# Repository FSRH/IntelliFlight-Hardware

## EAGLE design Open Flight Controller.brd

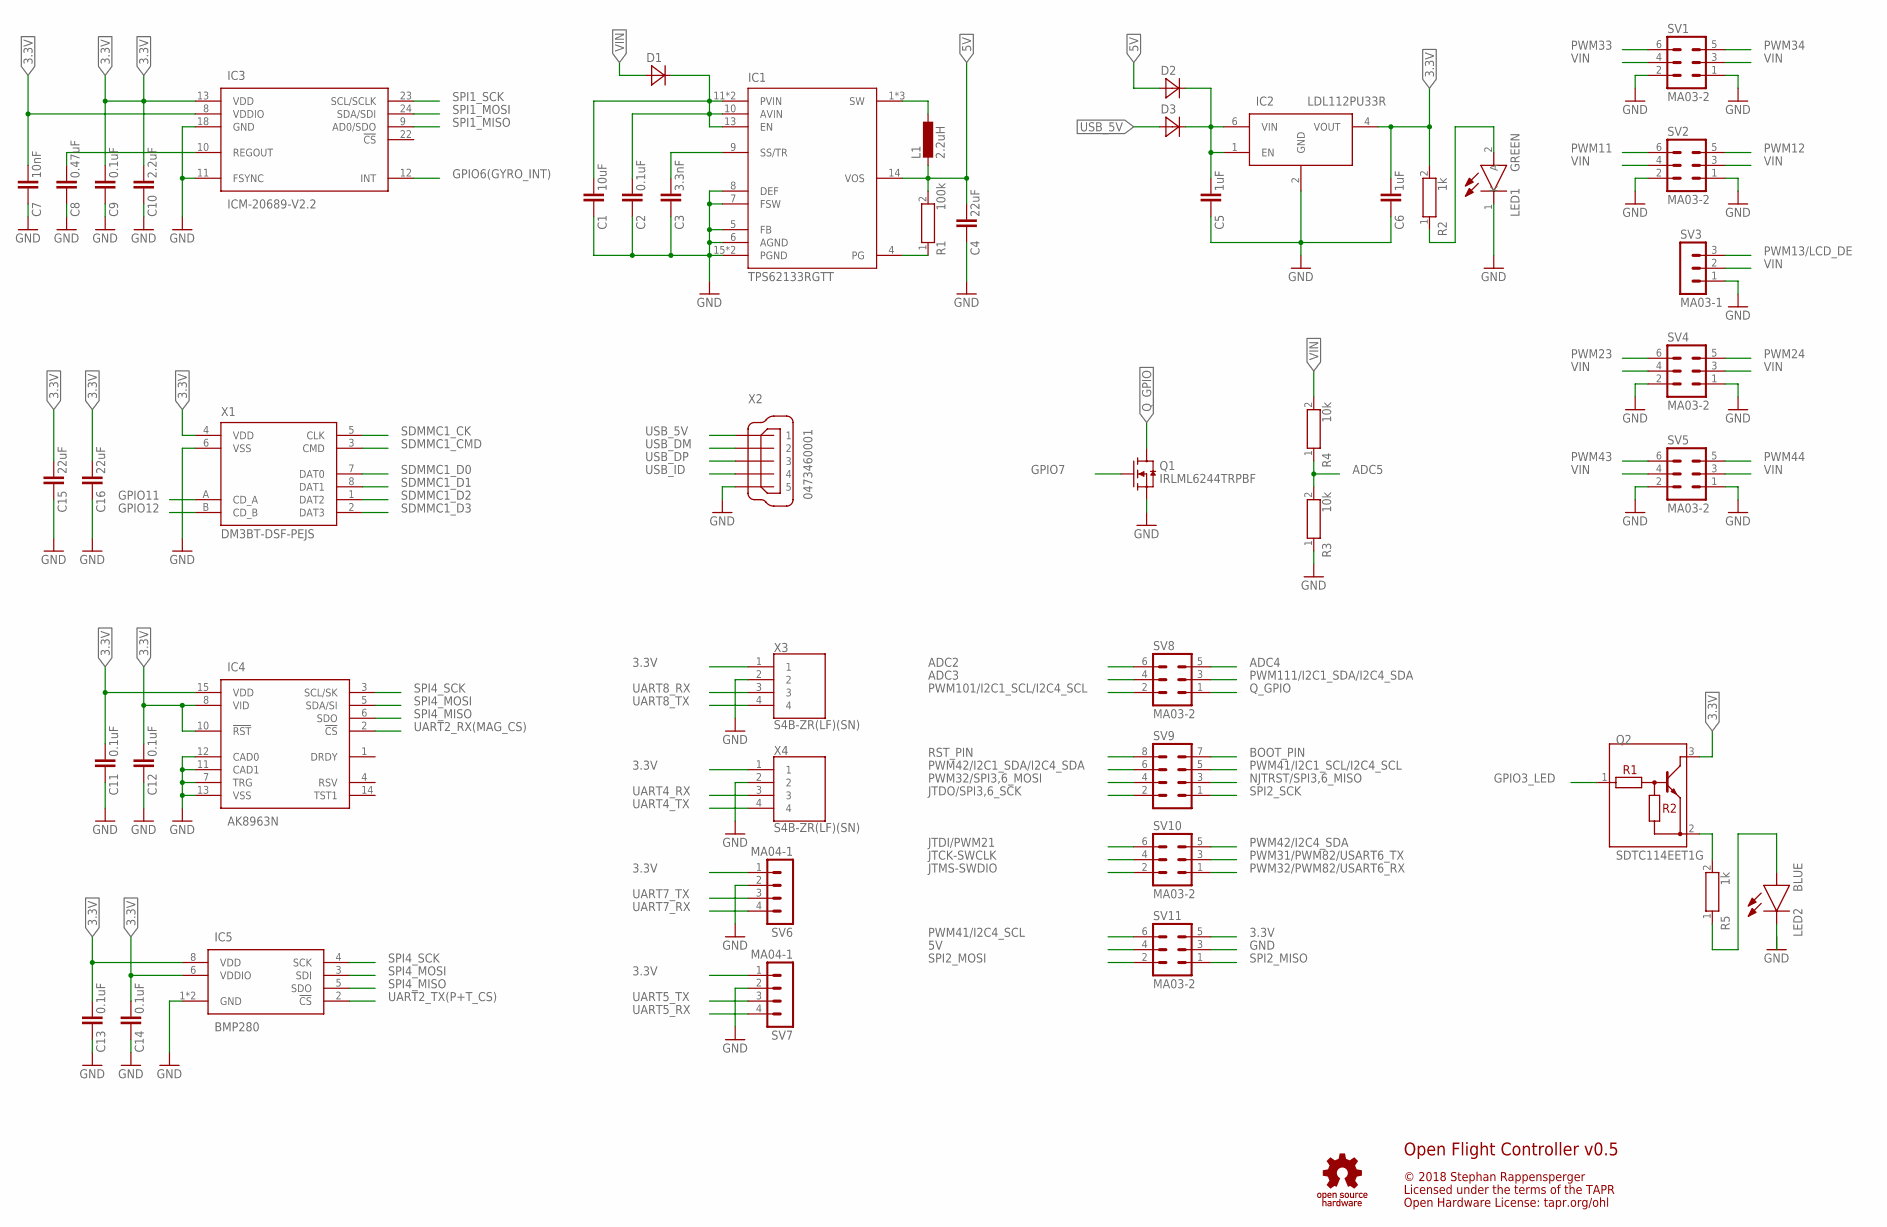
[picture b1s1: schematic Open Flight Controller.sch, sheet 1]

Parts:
C1: 10uF; CAPC1608X90N
C2, C9, C11, C12, C13, C14: 0.1uF; CAPC1608X90N
C3: 3.3nF; CAPC1608X90N
C4, C15, C16: 22uF; CAPC1608X100N
C5, C6: 1uF; CAPC1608X90N
C7: 10nF; CAPC1608X90N
C8: 0.47uF; CAPC1608X90N
C10: 2.2uF; CAPC1608X90N
D1, D2, D3: RBR3MM40ATR; PMDU
IC1: TPS62133RGTT; RGT16_1P7X1P7
IC2: LDL112PU33R; SON50P200X200X80-7N
IC3: ICM-20689-V2.2; QFN50P400X400X95-25N
IC4: AK8963N; QFN50P300X300X80-17N
IC5: BMP280; 8-PIN-METAL-LID-LGA
L1: 2.2uH; INDC2520X120N
LED1: GREEN; LEDC1608X100N
LED2: BLUE; LEDC1608X100N
Q1: IRLML6244TRPBF; SOT95P237X112-3N
Q2: SDTC114EET1G; SOT50P160X90-3N
R1: 100k; RESC1608X50N
R2, R5: 1k; RESC1608X50N
R3, R4: 10k; RESC1608X50N
SV1, SV2, SV4, SV5, SV8, SV10, SV11: MA03-2
SV3: MA03-1
SV6, SV7: MA04-1
SV9: MA04-2
X1: DM3BT-DSF-PEJS
X2: 0473460001
X3, X4: S4B-ZR(LF)(SN); SHDR4W50P0X150_1X4_750X600X370

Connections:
3.3V: C6.1, C7.1, C9.1, C10.1, C11.1, C12.1, C13.1, C14.1, C15.1, C16.1, IC2.4 (VOUT), IC3.8 (VDDIO), IC3.13 (VDD), IC4.8 (VID), IC4.10 (!RST), IC4.15 (VDD), IC5.6 (VDDIO), IC5.8 (VDD), Q2.3 (C), R2.2, SV6.1, SV7.1, SV11.5, X1.4 (VDD), X3.1, X4.1; also elsewhere on the board
5V: C4.1, D2.1 (A), IC1.14 (VOS), L1.1, R1.2, SV11.4
ADC2: SV8.6; also elsewhere on the board
ADC3: SV8.4; also elsewhere on the board
ADC4: SV8.5; also elsewhere on the board
ADC5: R3.2, R4.1; also elsewhere on the board
BOOT_PIN: SV9.7; also elsewhere on the board
GND: C1.2, C2.2, C3.2, C4.2, C5.2, C6.2, C7.2, C8.2, C9.2, C10.2, C11.2, C12.2, C13.2, C14.2, C15.2, C16.2, IC1.5 (FB), IC1.6 (AGND), IC1.7 (FSW), IC1.8 (DEF), IC1.15 (PGND), IC1.16 (PGND), IC2.2 (GND), IC3.11 (FSYNC), IC3.18 (GND), IC4.7 (TRG), IC4.11 (CAD1), IC4.12 (CAD0), IC4.13 (VSS), IC5.1 (GND), IC5.7 (GND), LED1.1 (K), LED2.1 (K), Q1.2 (S), R3.1, SV1.1, SV1.2, SV2.1, SV2.2, SV3.1, SV4.1, SV4.2, SV5.1, SV5.2, SV6.2, SV7.2, SV11.3, X1.6 (VSS), X2.5, X3.2, X4.2; also elsewhere on the board
GPIO3_LED: Q2.1 (B); also elsewhere on the board
GPIO6(GYRO_INT): IC3.12 (INT); also elsewhere on the board
GPIO7: Q1.1 (G); also elsewhere on the board
GPIO11: X1.A (CD_A); also elsewhere on the board
GPIO12: X1.B (CD_B); also elsewhere on the board
JTCK-SWCLK: SV10.4; also elsewhere on the board
JTDI/PWM21: SV10.6; also elsewhere on the board
JTDO/SPI3,6_SCK: SV9.2; also elsewhere on the board
JTMS-SWDIO: SV10.2; also elsewhere on the board
unnamed: C1.1, C2.1, D1.2 (C), IC1.10 (AVIN), IC1.11 (PVIN), IC1.12 (PVIN), IC1.13 (EN)
unnamed: IC1.1 (SW), IC1.2 (SW), IC1.3 (SW), L1.2
unnamed: C3.1, IC1.9 (SS/TR)
unnamed: IC1.4 (PG), R1.1
unnamed: C5.1, D2.2 (C), D3.2 (C), IC2.1 (EN), IC2.6 (VIN)
unnamed: LED1.2 (A), R2.1
unnamed: C8.1, IC3.10 (REGOUT)
unnamed: Q2.2 (E), R5.2
unnamed: LED2.2 (A), R5.1
NJTRST/SPI3,6_MISO: SV9.3; also elsewhere on the board
PWM11: SV2.6; also elsewhere on the board
PWM12: SV2.5; also elsewhere on the board
PWM13/LCD_DE: SV3.3; also elsewhere on the board
PWM23: SV4.6; also elsewhere on the board
PWM24: SV4.5; also elsewhere on the board
PWM31/PWM82/USART6_TX: SV10.3; also elsewhere on the board
PWM32/PWM82/USART6_RX: SV10.1; also elsewhere on the board
PWM32/SPI3,6_MOSI: SV9.4; also elsewhere on the board
PWM33: SV1.6; also elsewhere on the board
PWM34: SV1.5; also elsewhere on the board
PWM41/I2C1_SCL/I2C4_SCL: SV9.5; also elsewhere on the board
PWM41/I2C4_SCL: SV11.6; also elsewhere on the board
PWM42/I2C1_SDA/I2C4_SDA: SV9.6; also elsewhere on the board
PWM42/I2C4_SDA: SV10.5; also elsewhere on the board
PWM43: SV5.6; also elsewhere on the board
PWM44: SV5.5; also elsewhere on the board
PWM101/I2C1_SCL/I2C4_SCL: SV8.2; also elsewhere on the board
PWM111/I2C1_SDA/I2C4_SDA: SV8.3; also elsewhere on the board
Q_GPIO: Q1.3 (D), SV8.1
RST_PIN: SV9.8; also elsewhere on the board
SDMMC1_CK: X1.5 (CLK); also elsewhere on the board
SDMMC1_CMD: X1.3 (CMD); also elsewhere on the board
SDMMC1_D0: X1.7 (DAT0); also elsewhere on the board
SDMMC1_D1: X1.8 (DAT1); also elsewhere on the board
SDMMC1_D2: X1.1 (DAT2); also elsewhere on the board
SDMMC1_D3: X1.2 (DAT3); also elsewhere on the board
SPI1_MISO: IC3.9 (AD0/SDO); also elsewhere on the board
SPI1_MOSI: IC3.24 (SDA/SDI); also elsewhere on the board
SPI1_SCK: IC3.23 (SCL/SCLK); also elsewhere on the board
SPI2_MISO: SV11.1; also elsewhere on the board
SPI2_MOSI: SV11.2; also elsewhere on the board
SPI2_SCK: SV9.1; also elsewhere on the board
SPI4_MISO: IC4.6 (SDO), IC5.5 (SDO); also elsewhere on the board
SPI4_MOSI: IC4.5 (SDA/SI), IC5.3 (SDI); also elsewhere on the board
SPI4_SCK: IC4.3 (SCL/SK), IC5.4 (SCK); also elsewhere on the board
UART2_RX(MAG_CS): IC4.2 (!CS); also elsewhere on the board
UART2_TX(P+T_CS): IC5.2 (!CS); also elsewhere on the board
UART4_RX: X4.3; also elsewhere on the board
UART4_TX: X4.4; also elsewhere on the board
UART5_RX: SV7.4; also elsewhere on the board
UART5_TX: SV7.3; also elsewhere on the board
UART7_RX: SV6.4; also elsewhere on the board
UART7_TX: SV6.3; also elsewhere on the board
UART8_RX: X3.3; also elsewhere on the board
UART8_TX: X3.4; also elsewhere on the board
USB_5V: D3.1 (A), X2.1
USB_DM: X2.2; also elsewhere on the board
USB_DP: X2.3; also elsewhere on the board
USB_ID: X2.4; also elsewhere on the board
VIN: D1.1 (A), R4.2, SV1.3, SV1.4, SV2.3, SV2.4, SV3.2, SV4.3, SV4.4, SV5.3, SV5.4

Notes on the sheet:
Open Flight Controller v0.5
© 2018 Stephan Rappensperger
Licensed under the terms of the TAPR
Open Hardware License: tapr.org/ohl

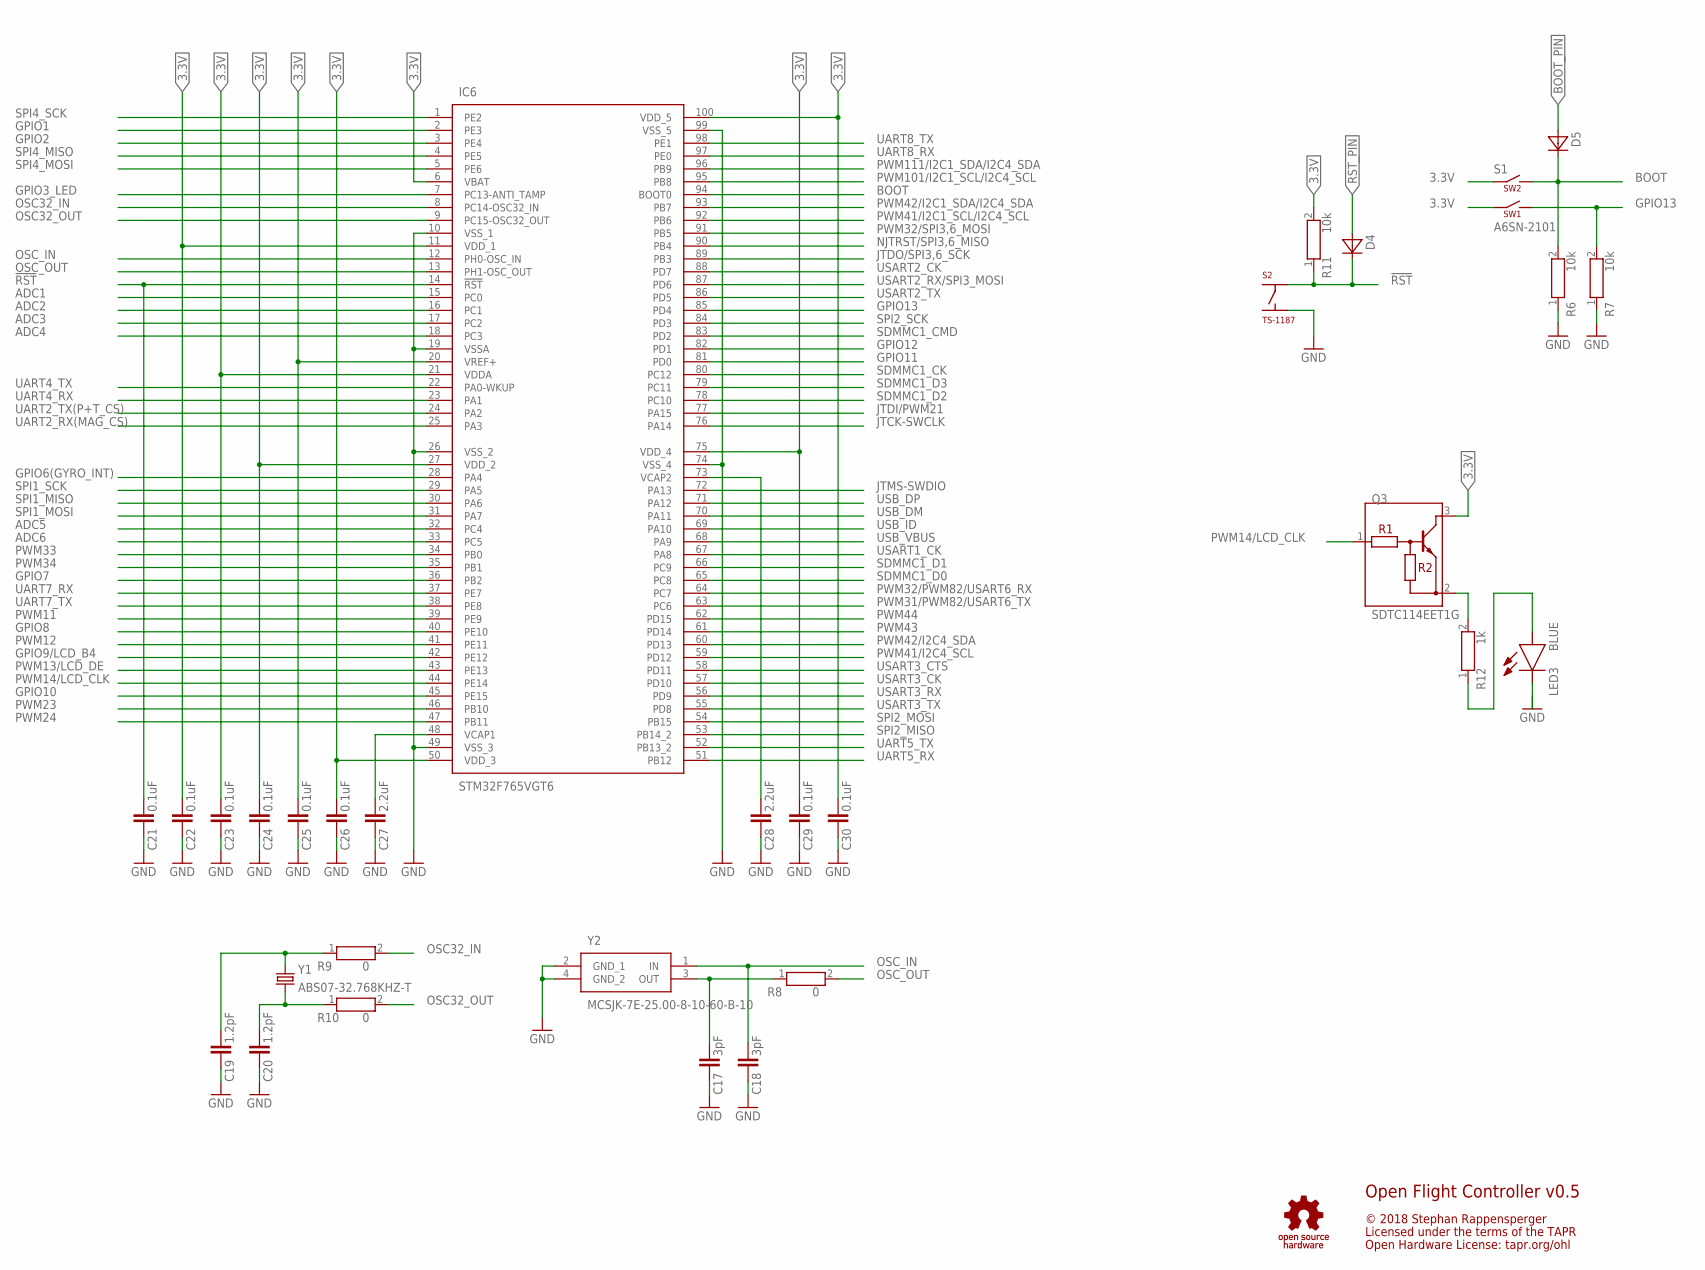
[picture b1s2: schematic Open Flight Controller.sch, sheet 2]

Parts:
C17, C18: 3pF; CAPC1608X90N
C19, C20: 1.2pF; CAPC1608X90N
C21, C22, C23, C24, C25, C26, C29, C30: 0.1uF; CAPC1608X90N
C27, C28: 2.2uF; CAPC1608X90N
D4, D5: RBR3MM40ATR; PMDU
IC6: STM32F765VGT6; QFP50P1600X1600X160-100N
LED3: BLUE; LEDC1608X100N
Q3: SDTC114EET1G; SOT50P160X90-3N
R6, R7, R11: 10k; RESC1608X50N
R8, R9, R10: 0; RESC1608X50N
R12: 1k; RESC1608X50N
S1: A6SN-2101; SOP254P930X455-4N
S2: TS-1187; TS-1187-3.8
Y1: ABS07-32.768KHZ-T; ABS-07
Y2: MCSJK-7E-25.00-8-10-60-B-10; MCSJK7E2500101060B10

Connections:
3.3V: C22.1, C23.1, C24.1, C25.1, C26.1, C29.1, C30.1, IC6.6 (VBAT), IC6.11 (VDD_1), IC6.20 (VREF+), IC6.21 (VDDA), IC6.27 (VDD_2), IC6.50 (VDD_3), IC6.75 (VDD_4), IC6.100 (VDD_5), Q3.3 (C), R11.2, S1.1 (COM_1), S1.2 (COM_2); also elsewhere on the board
!RST: C21.1, D4.2 (C), IC6.14 (!RST), R11.1, S2.P$2
ADC1: IC6.15 (PC0)
ADC2: IC6.16 (PC1); also elsewhere on the board
ADC3: IC6.17 (PC2); also elsewhere on the board
ADC4: IC6.18 (PC3); also elsewhere on the board
ADC5: IC6.32 (PC4); also elsewhere on the board
ADC6: IC6.33 (PC5)
BOOT: D5.2 (C), IC6.94 (BOOT0), R6.2, S1.4 (NO_1)
BOOT_PIN: D5.1 (A); also elsewhere on the board
GND: C17.2, C18.2, C19.2, C20.2, C21.2, C22.2, C23.2, C24.2, C25.2, C26.2, C27.2, C28.2, C29.2, C30.2, IC6.10 (VSS_1), IC6.19 (VSSA), IC6.26 (VSS_2), IC6.49 (VSS_3), IC6.74 (VSS_4), IC6.99 (VSS_5), LED3.1 (K), R6.1, R7.1, S2.P$4, Y2.2 (GND_1), Y2.4 (GND_2); also elsewhere on the board
GPIO1: IC6.2 (PE3)
GPIO2: IC6.3 (PE4)
GPIO3_LED: IC6.7 (PC13-ANTI_TAMP); also elsewhere on the board
GPIO6(GYRO_INT): IC6.28 (PA4); also elsewhere on the board
GPIO7: IC6.36 (PB2); also elsewhere on the board
GPIO8: IC6.40 (PE10)
GPIO9/LCD_B4: IC6.42 (PE12)
GPIO10: IC6.45 (PE15)
GPIO11: IC6.81 (PD0); also elsewhere on the board
GPIO12: IC6.82 (PD1); also elsewhere on the board
GPIO13: IC6.85 (PD4), R7.2, S1.3 (NO_2)
JTCK-SWCLK: IC6.76 (PA14); also elsewhere on the board
JTDI/PWM21: IC6.77 (PA15); also elsewhere on the board
JTDO/SPI3,6_SCK: IC6.89 (PB3); also elsewhere on the board
JTMS-SWDIO: IC6.72 (PA13); also elsewhere on the board
unnamed: C17.1, R8.1, Y2.3 (OUT)
unnamed: C27.1, IC6.48 (VCAP1)
unnamed: C28.1, IC6.73 (VCAP2)
unnamed: Q3.2 (E), R12.2
unnamed: C20.1, R10.1, Y1.2
unnamed: C19.1, R9.1, Y1.1
unnamed: LED3.2 (A), R12.1
NJTRST/SPI3,6_MISO: IC6.90 (PB4); also elsewhere on the board
OSC32_IN: IC6.8 (PC14-OSC32_IN), R9.2
OSC32_OUT: IC6.9 (PC15-OSC32_OUT), R10.2
OSC_IN: C18.1, IC6.12 (PH0-OSC_IN), Y2.1 (IN)
OSC_OUT: IC6.13 (PH1-OSC_OUT), R8.2
PWM11: IC6.39 (PE9); also elsewhere on the board
PWM12: IC6.41 (PE11); also elsewhere on the board
PWM13/LCD_DE: IC6.43 (PE13); also elsewhere on the board
PWM14/LCD_CLK: IC6.44 (PE14), Q3.1 (B)
PWM23: IC6.46 (PB10); also elsewhere on the board
PWM24: IC6.47 (PB11); also elsewhere on the board
PWM31/PWM82/USART6_TX: IC6.63 (PC6); also elsewhere on the board
PWM32/PWM82/USART6_RX: IC6.64 (PC7); also elsewhere on the board
PWM32/SPI3,6_MOSI: IC6.91 (PB5); also elsewhere on the board
PWM33: IC6.34 (PB0); also elsewhere on the board
PWM34: IC6.35 (PB1); also elsewhere on the board
PWM41/I2C1_SCL/I2C4_SCL: IC6.92 (PB6); also elsewhere on the board
PWM41/I2C4_SCL: IC6.59 (PD12); also elsewhere on the board
PWM42/I2C1_SDA/I2C4_SDA: IC6.93 (PB7); also elsewhere on the board
PWM42/I2C4_SDA: IC6.60 (PD13); also elsewhere on the board
PWM43: IC6.61 (PD14); also elsewhere on the board
PWM44: IC6.62 (PD15); also elsewhere on the board
PWM101/I2C1_SCL/I2C4_SCL: IC6.95 (PB8); also elsewhere on the board
PWM111/I2C1_SDA/I2C4_SDA: IC6.96 (PB9); also elsewhere on the board
RST_PIN: D4.1 (A); also elsewhere on the board
SDMMC1_CK: IC6.80 (PC12); also elsewhere on the board
SDMMC1_CMD: IC6.83 (PD2); also elsewhere on the board
SDMMC1_D0: IC6.65 (PC8); also elsewhere on the board
SDMMC1_D1: IC6.66 (PC9); also elsewhere on the board
SDMMC1_D2: IC6.78 (PC10); also elsewhere on the board
SDMMC1_D3: IC6.79 (PC11); also elsewhere on the board
SPI1_MISO: IC6.30 (PA6); also elsewhere on the board
SPI1_MOSI: IC6.31 (PA7); also elsewhere on the board
SPI1_SCK: IC6.29 (PA5); also elsewhere on the board
SPI2_MISO: IC6.53 (PB14_2); also elsewhere on the board
SPI2_MOSI: IC6.54 (PB15); also elsewhere on the board
SPI2_SCK: IC6.84 (PD3); also elsewhere on the board
SPI4_MISO: IC6.4 (PE5); also elsewhere on the board
SPI4_MOSI: IC6.5 (PE6); also elsewhere on the board
SPI4_SCK: IC6.1 (PE2); also elsewhere on the board
UART2_RX(MAG_CS): IC6.25 (PA3); also elsewhere on the board
UART2_TX(P+T_CS): IC6.24 (PA2); also elsewhere on the board
UART4_RX: IC6.23 (PA1); also elsewhere on the board
UART4_TX: IC6.22 (PA0-WKUP); also elsewhere on the board
UART5_RX: IC6.51 (PB12); also elsewhere on the board
UART5_TX: IC6.52 (PB13_2); also elsewhere on the board
UART7_RX: IC6.37 (PE7); also elsewhere on the board
UART7_TX: IC6.38 (PE8); also elsewhere on the board
UART8_RX: IC6.97 (PE0); also elsewhere on the board
UART8_TX: IC6.98 (PE1); also elsewhere on the board
USART1_CK: IC6.67 (PA8)
USART2_CK: IC6.88 (PD7)
USART2_RX/SPI3_MOSI: IC6.87 (PD6)
USART2_TX: IC6.86 (PD5)
USART3_CK: IC6.57 (PD10)
USART3_CTS: IC6.58 (PD11)
USART3_RX: IC6.56 (PD9)
USART3_TX: IC6.55 (PD8)
USB_DM: IC6.70 (PA11); also elsewhere on the board
USB_DP: IC6.71 (PA12); also elsewhere on the board
USB_ID: IC6.69 (PA10); also elsewhere on the board
USB_VBUS: IC6.68 (PA9)

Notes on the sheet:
Open Flight Controller v0.5
© 2018 Stephan Rappensperger
Licensed under the terms of the TAPR
Open Hardware License: tapr.org/ohl

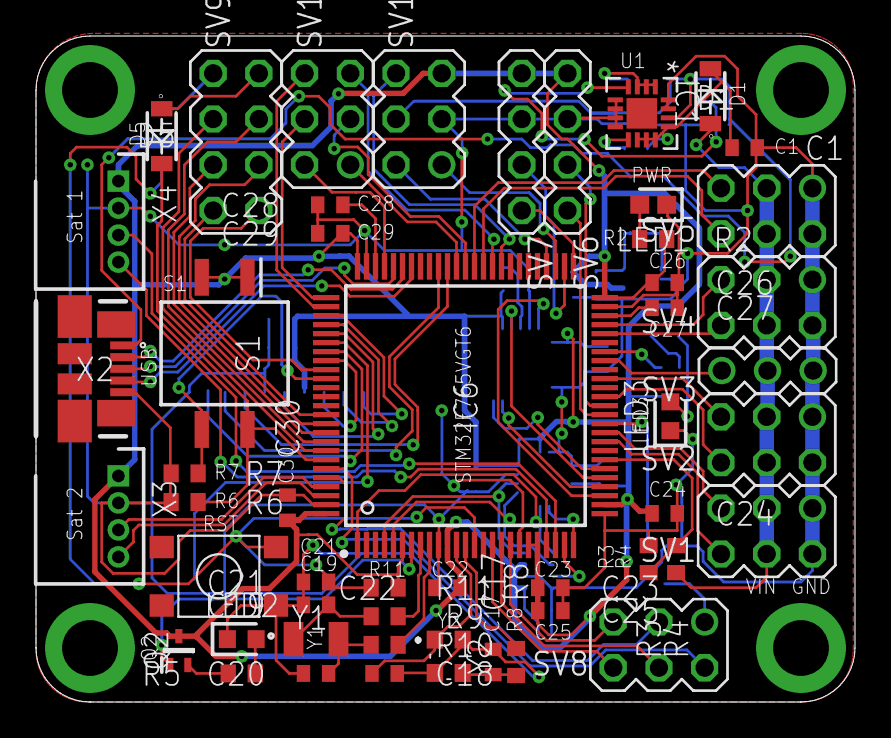
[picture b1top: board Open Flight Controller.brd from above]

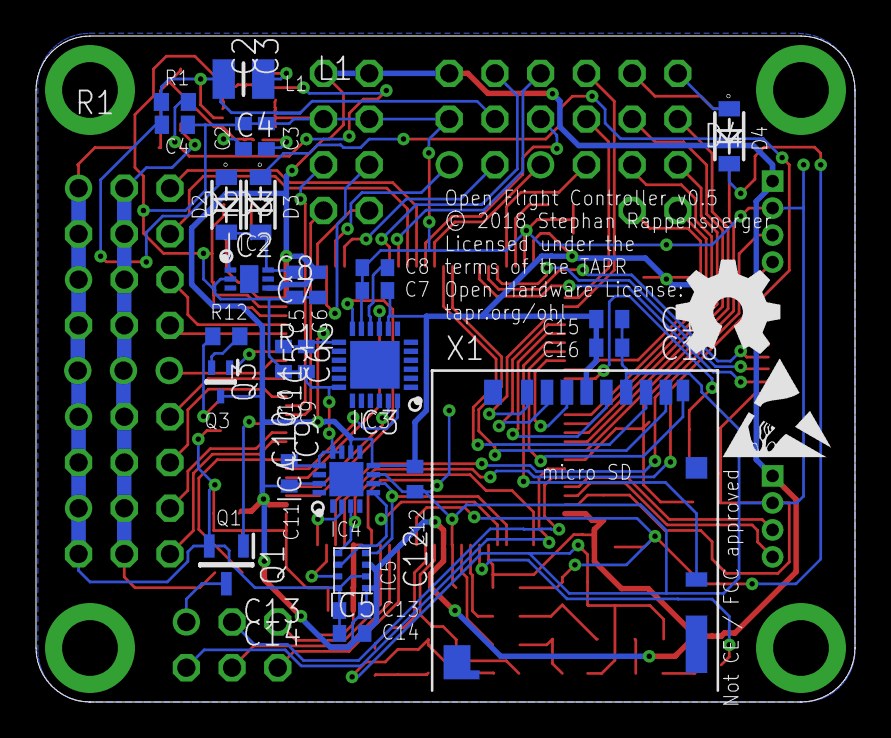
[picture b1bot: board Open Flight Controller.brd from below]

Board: 2 copper layers, 45.5 x 37.0 mm, 79 parts (28 on the bottom side), 92 nets.

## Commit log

2018-08-20 add exports
2018-09-11 Added reset-pin and pwm-led
